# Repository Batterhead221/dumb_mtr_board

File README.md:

# DUMB_MTR_BOARD

Standalone stepper motor controller board with local forward/reverse jog buttons, speed adjustment, status LEDs, and a TMC stepper driver module.

Motor controller board

DUMB_MTR Board provides a small standalone interface for driving a stepper motor.

Core functions:

* Power input from 5-24V
* Stepper motor output connector
* Forward and reverse jog buttons
* Speed adjustment potentiometer
* RGB/status LEDs
* UART header for driver configuration/debugging
* Manual local control without needing the Brain_Board

Input power:     5-24V
Motor driver:    TMC stepper driver module
Controls:        FWD / REV buttons
Adjustment:      Speed potentiometer
Indicators:      Power / direction LEDs
Motor output:    4-pin stepper connector
Logic rail:      On-board 3.3V regulator

# DUMB_MTR Board

A compact standalone stepper motor control board built around a TMC stepper driver module.

This board is designed as a simple hands-on motor controller with local direction controls, speed adjustment, motor output, status LEDs, and a selectable input power source.

## System Role

```text
5-24V input power
        ↓
DUMB_MTR_BOARD
        ↓ local FWD / REV buttons + speed potentiometer
TMC stepper driver module
        ↓
4-wire stepper motor
```

DUMB_MTR_BOARD is the controller and driver carrier for a simple local stepper motor setup.

## Key Specs

| Item | Value |
|---|---|
| Board role | Standalone stepper motor controller |
| Input power | 5-24V |
| Motor driver | TMC stepper driver module |
| Motor output | 4-pin stepper connector |
| Local controls | Forward / reverse jog buttons |
| Adjustment | Speed potentiometer |
| Indicators | Power / direction / status LEDs |
| Debug/config | UART header |
| Logic rail | On-board 3.3V regulator |
| Main use | Manual motor control and driver testing |

## Main Features

- 5-24V input power
- TMC stepper driver module footprint/header
- 4-pin stepper motor output connector
- Forward jog button
- Reverse jog button
- Speed adjustment potentiometer
- RGB/status LED indicators
- UART header for driver configuration/debugging
- On-board 3.3V logic regulation
- Manual local motor control without BRAIN_BOARD
- Compact bench-testable layout

## Controls

### Forward / Reverse Jog

The board includes local direction/jog buttons for manual control.

```text
FWD button → forward jog command
REV button → reverse jog command
```

### Speed Potentiometer

The speed potentiometer provides a local analog adjustment for motor speed or step timing.

```text
Potentiometer → speed / rate control input
```

Firmware or local control logic should map the potentiometer reading into an appropriate step rate.

## Motor Driver

The board is built around a TMC stepper driver module.

Typical driver-side signals may include:

| Signal | Purpose |
|---|---|
| STEP | Step pulse input |
| DIR | Direction input |
| EN | Driver enable |
| UART | Driver configuration/debugging |
| VM | Motor supply input |
| GND | Shared ground |
| A1/A2/B1/B2 | Stepper coil outputs |

Confirm the exact TMC module pinout before installing a driver module.

## Power Architecture

```text
5-24V input
    ↓
motor-driver VM rail
    ↓
TMC stepper driver module
    ↓
motor phase outputs
```

Logic power is generated locally:

```text
input power → 3.3V regulator → local logic/control rail
```

## Motor Output

The motor output is a 4-pin connector for a bipolar stepper motor.

Typical coil mapping:

```text
Coil A → A1 / A2
Coil B → B1 / B2
```

Always verify motor coil pairs with a meter before connecting the motor.

## UART Header

The UART header is intended for TMC driver configuration, tuning, or debug access.

```text
UART TX/RX
GND
logic reference
```

Match voltage levels before connecting any external USB-to-UART adapter.

## Design Notes

- Keep motor-current paths short and wide.
- Keep motor VM routing away from low-level control signals where practical.
- Verify the TMC driver module orientation before power-up.
- Confirm the potentiometer direction and firmware mapping during bring-up.
- Start with current-limited input power during first tests.
- Do not hot-plug the stepper motor while the driver is powered.
- Keep UART/debug access available for driver tuning.

## Bring-Up Checklist

1. Inspect soldering and connector orientation.
2. Confirm no short between input power and GND.
3. Confirm no short between 3.3V and GND.
4. Power the board with a current-limited supply.
5. Verify the 3.3V rail.
6. Confirm power/status LEDs behave as expected.
7. Verify the TMC driver module orientation.
8. Connect UART/debug if driver configuration is needed.
9. Confirm FWD and REV buttons are read correctly.
10. Confirm the speed potentiometer changes the command rate.
11. Connect the motor after verifying coil pairs.
12. Start with low current and slow speed before full operation.

## Repository Output Images

Expected image paths for GitHub README rendering:

```text
Outputs/
  IMG/
    3D-T.png
    3D-B.png
    SCHEMATIC.png
    L1-SIG.png
    L2-GND.png
```

## Safety / Design Note

DUMB_MTR_BOARD handles motor power. Verify input polarity, motor wiring, driver orientation, current settings, and thermal behavior before running the motor under load.

Designed & engineered by Brandon Shelly

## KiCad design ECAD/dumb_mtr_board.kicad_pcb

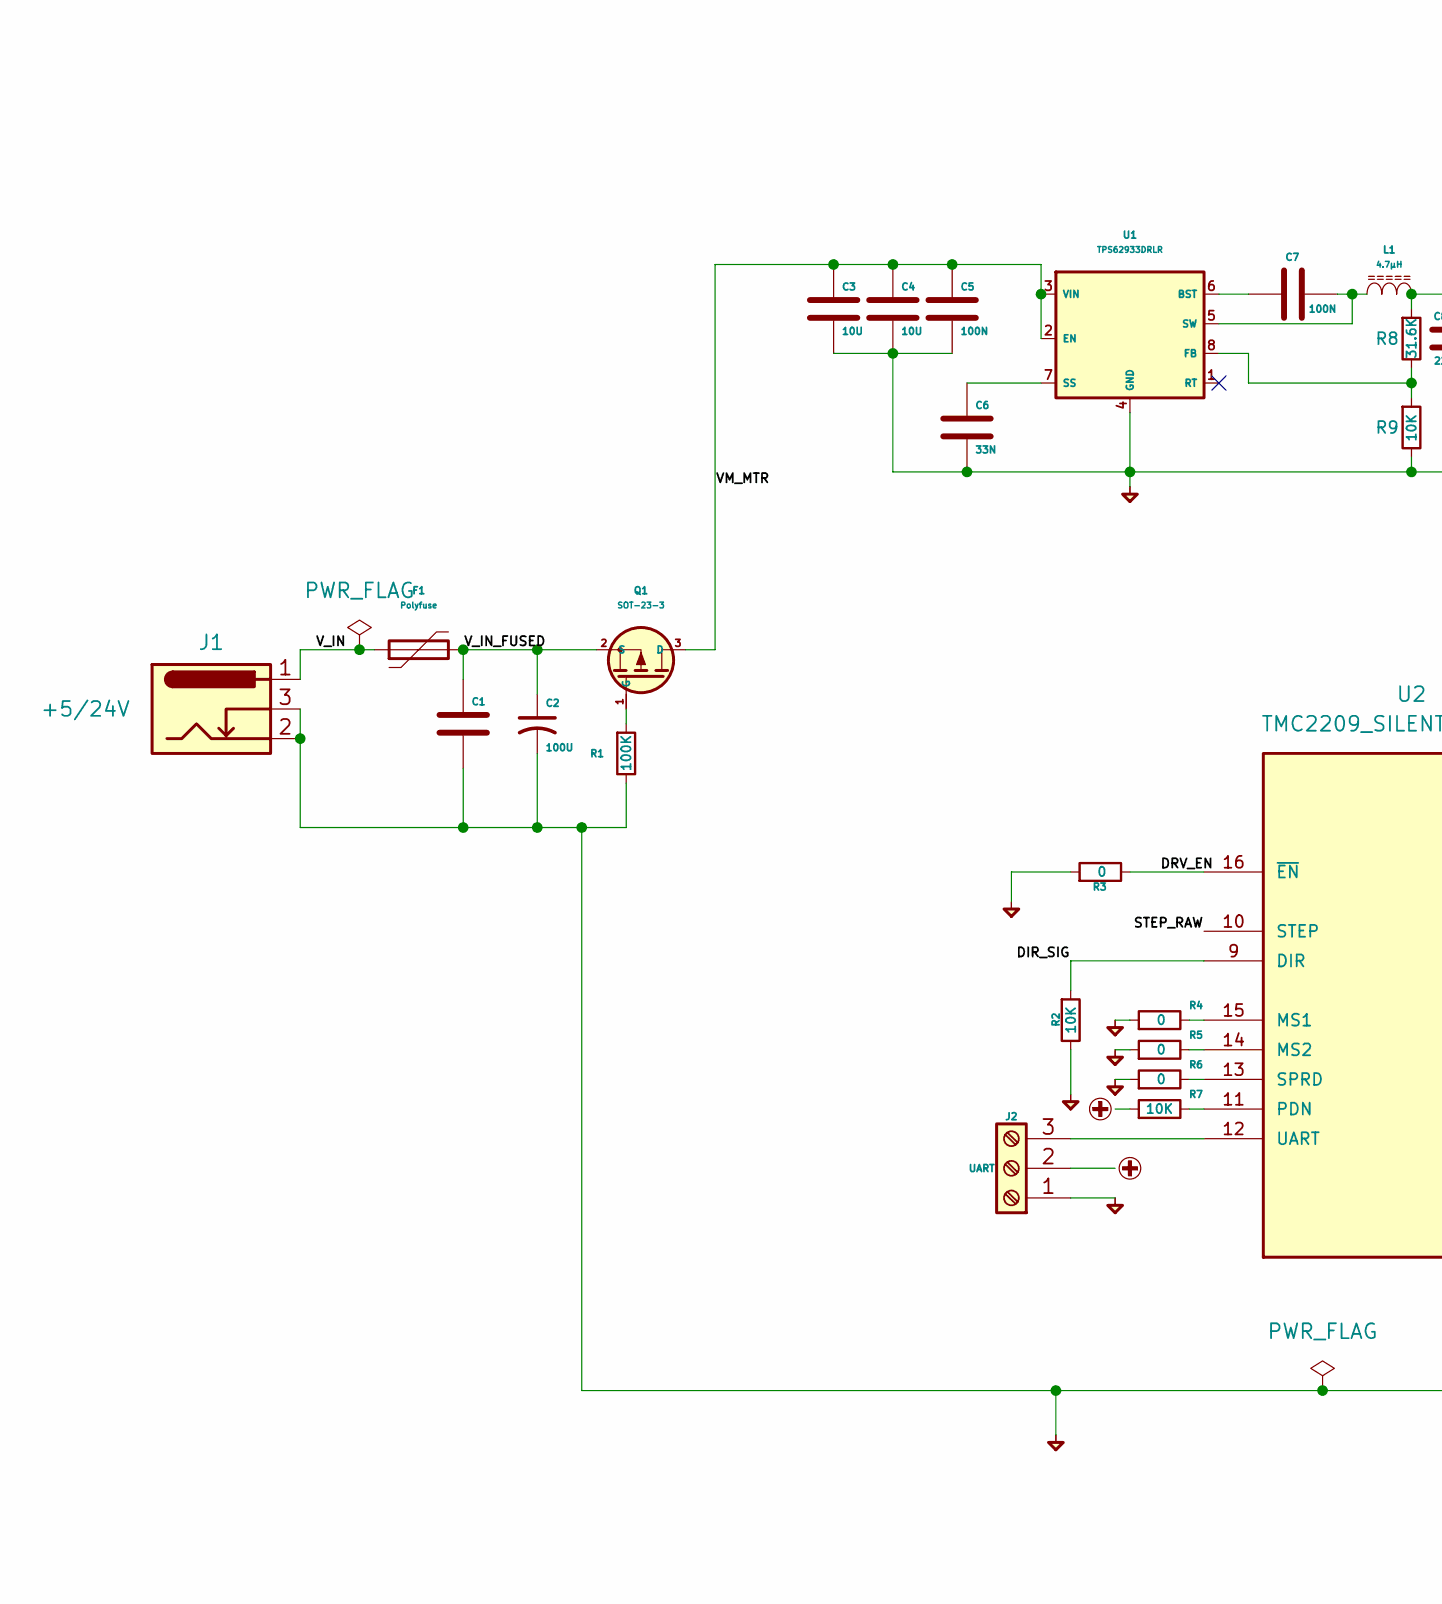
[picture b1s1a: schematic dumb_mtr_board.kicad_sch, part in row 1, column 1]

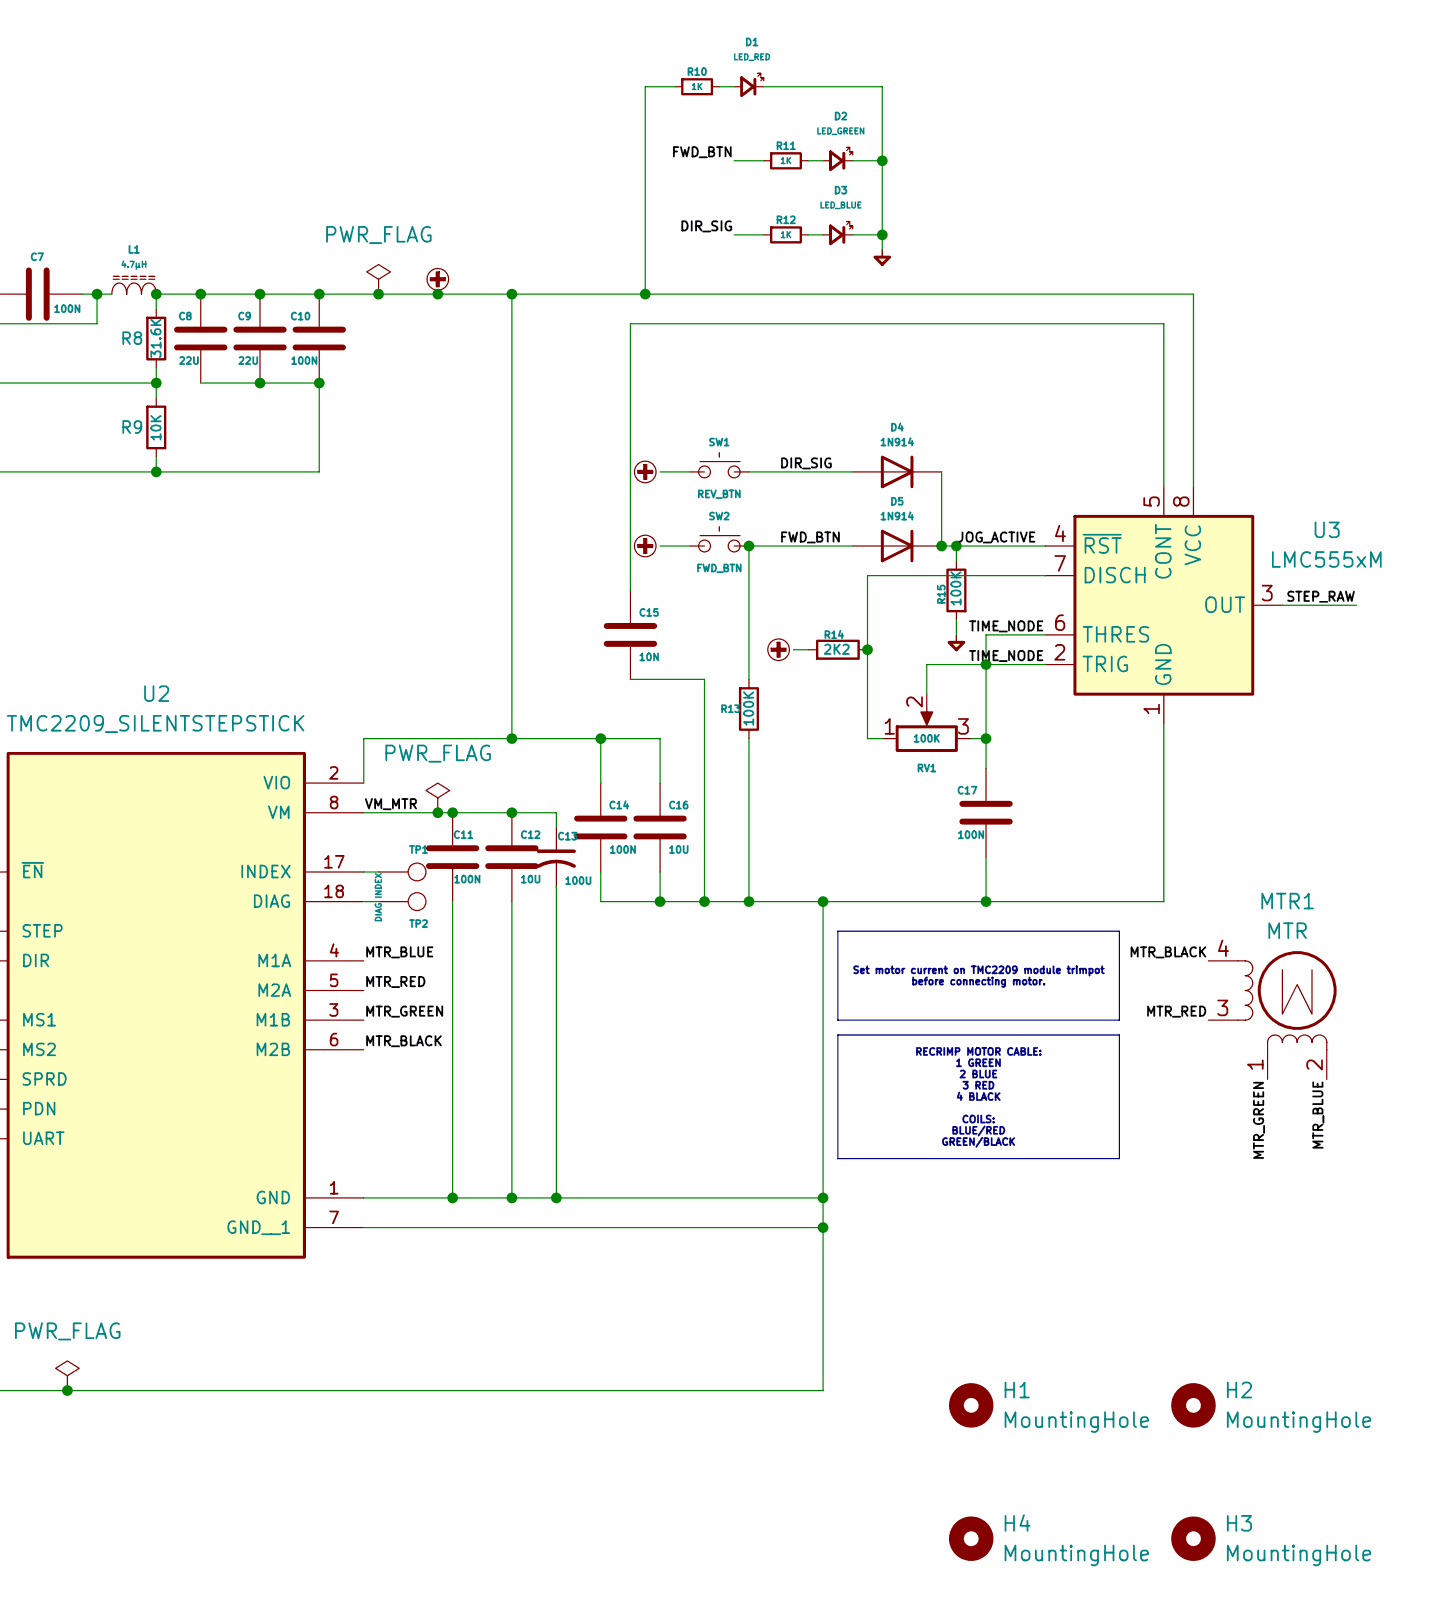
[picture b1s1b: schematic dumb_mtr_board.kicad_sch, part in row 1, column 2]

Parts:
C1, C5, C7, C10, C11, C14, C17: 100N; C_0603_1608Metric
C2, C13: 100U; PCAP_8x11_5-THRU-ELECT_NCA
C3, C4, C12, C16: 10U; C_0805_2012Metric
C6: 33N; C_0603_1608Metric
C8, C9: 22U; C_1206_3216Metric
C15: 10N; C_0603_1608Metric
D1: LED_RED; LED_0603_1608Metric
D2: LED_GREEN; LED_0603_1608Metric
D3: LED_BLUE; LED_0603_1608Metric
D4, D5: 1N914; D_0603_1608Metric
F1: Polyfuse; Fuse_1206_3216Metric
H1, H2, H3, H4: MountingHole; MountingHole_2.2mm_M2_ISO14580_Pad_TopBottom
J1: +5/24V; BarrelJack_Wuerth_6941xx301002
J2: UART; PinHeader_1x03_P2.54mm_Vertical
L1: 4.7µH; L_SRP5030TA4R7M
MTR1: MTR; MTA-4
Q1: SOT-23-3; TSOT-23
R1, R13, R15: 100K; R_0603_1608Metric
R2, R7, R9: 10K; R_0603_1608Metric
R3, R4, R5, R6: 0; R_0603_1608Metric
R8: 31.6K; R_0603_1608Metric
R10, R11, R12: 1K; R_0603_1608Metric
R14: 2K2; R_0603_1608Metric
RV1: 100K; TRIM_3296W-1-104LF
SW1: REV_BTN; SW_PUSH_6mm
SW2: FWD_BTN; SW_PUSH_6mm
TP1: INDEX; TestPoint_Pad_2.0x2.0mm
TP2: DIAG; TestPoint_Pad_2.0x2.0mm
U1: TPS62933DRLR; SOT-583-8
U2: TMC2209_SILENTSTEPSTICK; MODULE_TMC2209_SILENTSTEPSTICK; PARTREV 1.20
U3: LMC555xM; SOIC-8_3.9x4.9mm_P1.27mm

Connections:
+3.3V: C8.2, C9.2, C10.2, C14.2, C16.1, J2.2, L1.2, R7.1, R8.1, R10.1, R14.1, SW1.1, SW2.1, U2.2 (VIO), U3.8 (VCC)
/DIR_SIG: D4.2 (A), R2.1, R12.1, SW1.2, U2.9 (DIR)
/DRV_EN: R3.2, U2.16 (~EN)
/FWD_BTN: D5.2 (A), R11.1, R13.1, SW2.2
/JOG_ACTIVE: D4.1 (K), D5.1 (K), R15.2, U3.4 (~RST)
/MTR_BLACK: MTR1.4, U2.6 (M2B)
/MTR_BLUE: MTR1.2 (-_2), U2.4 (M1A)
/MTR_GREEN: MTR1.1, U2.3 (M1B)
/MTR_RED: MTR1.3, U2.5 (M2A)
/STEP_RAW: U2.10 (STEP), U3.3 (OUT)
/TIME_NODE: C17.2, RV1.2, RV1.3, U3.2 (TRIG), U3.6 (THRES)
/VM_MTR: C3.1, C4.1, C5.1, C11.2, C12.1, C13.1, Q1.3 (D), U1.2 (EN), U1.3 (VIN), U2.8 (VM)
/V_IN: F1.1, J1.1
/V_IN_FUSED: C1.1, C2.1, F1.2, Q1.2 (S)
GND: C1.2, C2.2, C3.2, C4.2, C5.2, C6.2, C8.1, C9.1, C10.1, C11.1, C12.2, C13.2, C14.1, C15.2, C16.2, C17.1, D1.1 (K), D2.1 (K), D3.1 (K), J1.2, J1.3, J2.1, R1.2, R2.2, R3.1, R4.1, R5.1, R6.1, R9.2, R13.2, R15.1, U1.4 (GND), U2.1 (GND), U2.7 (GND__1), U3.1 (GND)
unnamed: D1.2 (A), R10.2
unnamed: D2.2 (A), R11.2
unnamed: D3.2 (A), R12.2
unnamed: J2.3, U2.12 (UART)
unnamed: Q1.1 (G), R1.1
unnamed: C7.1, U1.6 (BST)
unnamed: R8.2, R9.1, U1.8 (FB)
unnamed: C6.1, U1.7 (SS)
unnamed: C7.2, L1.1, U1.5 (SW)
unnamed: TP2.1 (1_1), U2.18 (DIAG)
unnamed: TP1.1 (1_1), U2.17 (INDEX)
unnamed: R4.2, U2.15 (MS1)
unnamed: R5.2, U2.14 (MS2)
unnamed: R7.2, U2.11 (PDN)
unnamed: R6.2, U2.13 (SPRD)
unnamed: C15.1, U3.5 (CONT)
unnamed: R14.2, RV1.1, U3.7 (DISCH)

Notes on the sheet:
Set motor current on TMC2209 module trimpot before connecting motor.
RECRIMP MOTOR CABLE: 1 GREEN 2 BLUE 3 RED 4 BLACK COILS: BLUE/RED GREEN/BLACK

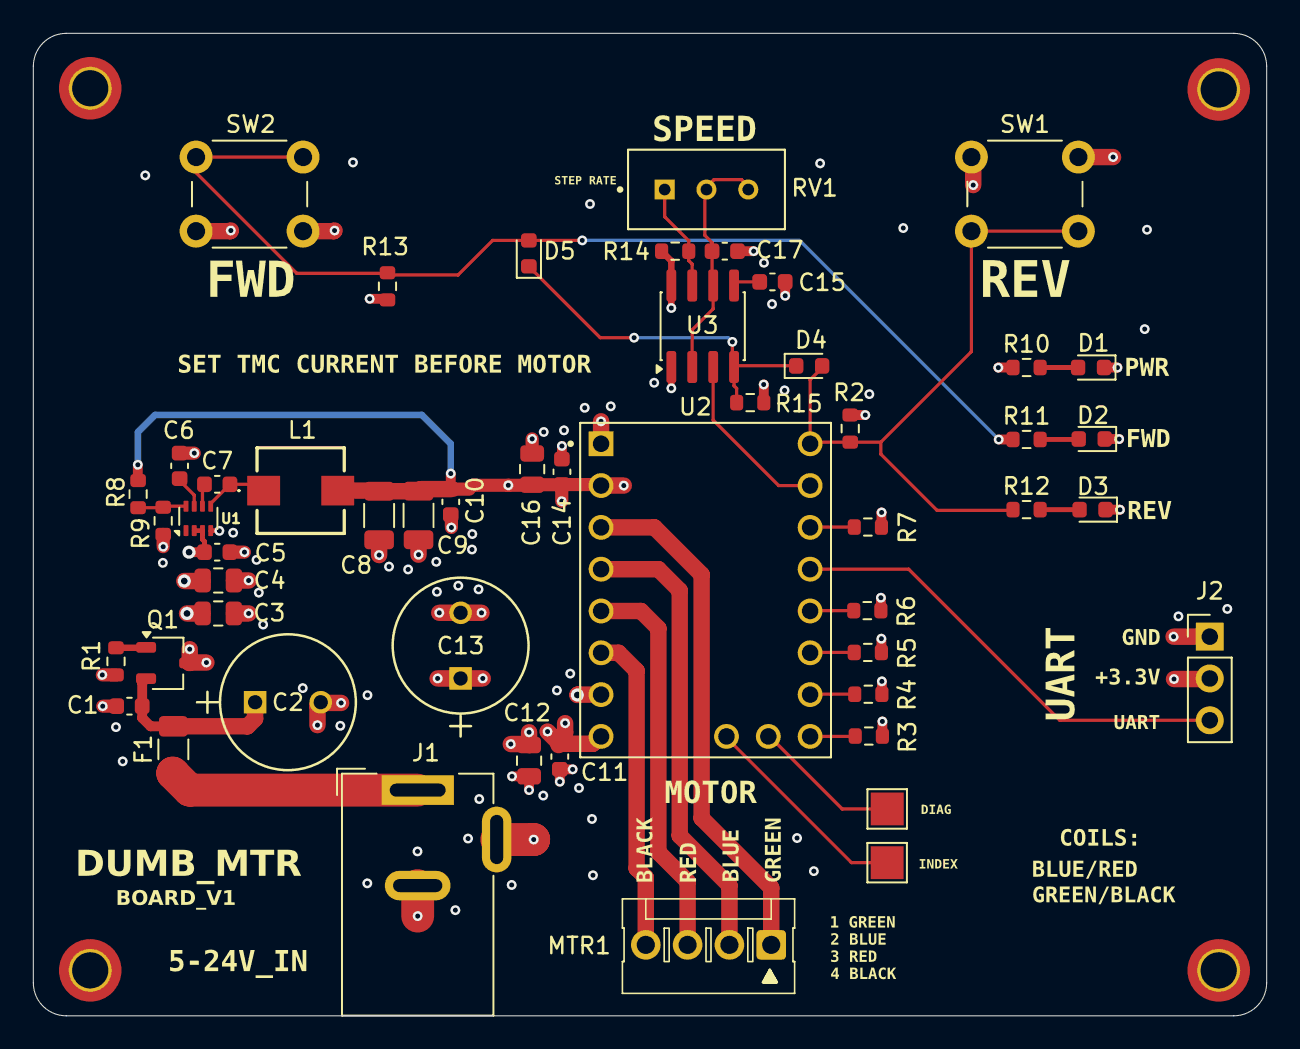
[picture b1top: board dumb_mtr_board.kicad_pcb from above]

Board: 4 copper layers, 74.9 x 59.7 mm, 55 parts (0 on the bottom side), 32 nets.

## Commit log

2026-05-06 new repo
2026-05-07 readme
2026-05-13 Revised repo
2026-05-13 Added stitching vias
2026-05-14 switched connectors
2026-05-24 repo
2026-05-24 cont.
2026-05-24 next
